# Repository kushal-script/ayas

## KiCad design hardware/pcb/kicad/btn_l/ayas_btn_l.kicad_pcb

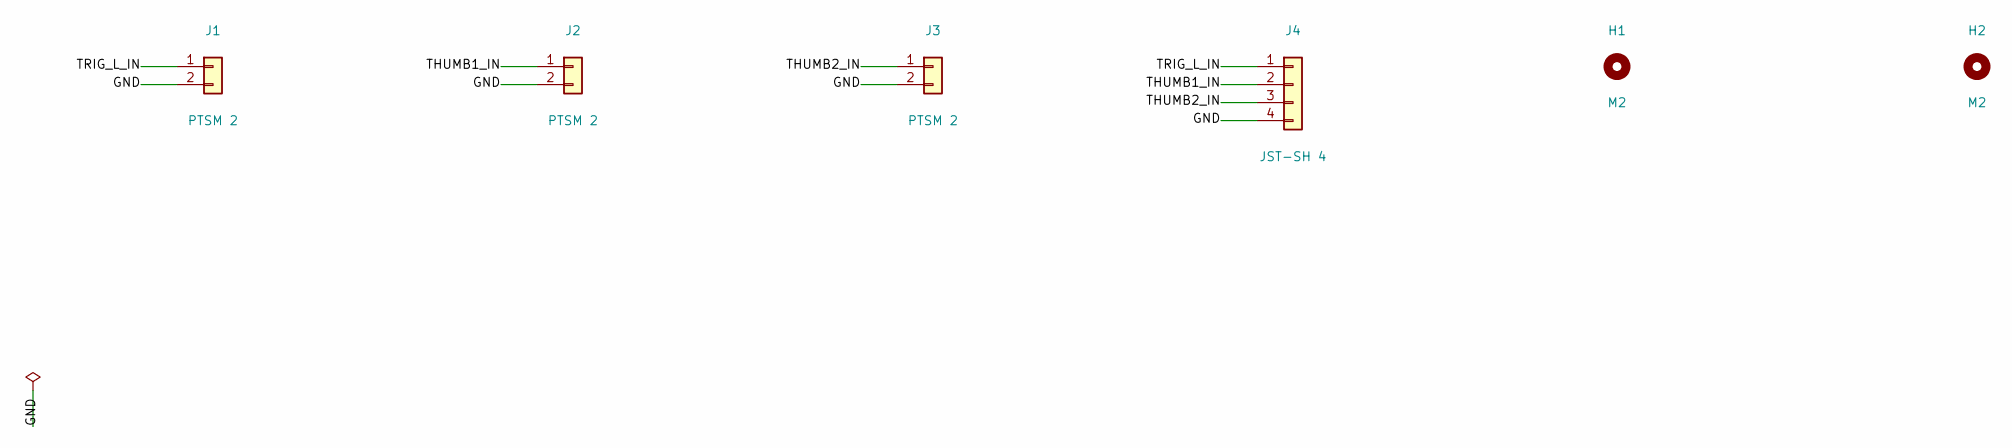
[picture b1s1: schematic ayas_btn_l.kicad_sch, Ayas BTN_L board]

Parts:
H1, H2: M2; MountingHole_2.2mm_M2
J1, J2, J3: PTSM 2; TerminalBlock_Phoenix_PTSM-0,5-2-2.5-H-THR_1x02_P2.50mm_Hor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; MPN PTSM 0,5/ 2-2,5-H THR (Phoenix Contact)
J4: JST-SH 4; JST_SH_SM04B-SRSS-TB_1x04-1MP_P1.00mm_Horizontal; MPN SM04B-SRSS-TB (JST)

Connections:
GND: J1.2, J2.2, J3.2, J4.4
THUMB1_IN: J2.1, J4.2
THUMB2_IN: J3.1, J4.3
TRIG_L_IN: J1.1, J4.1

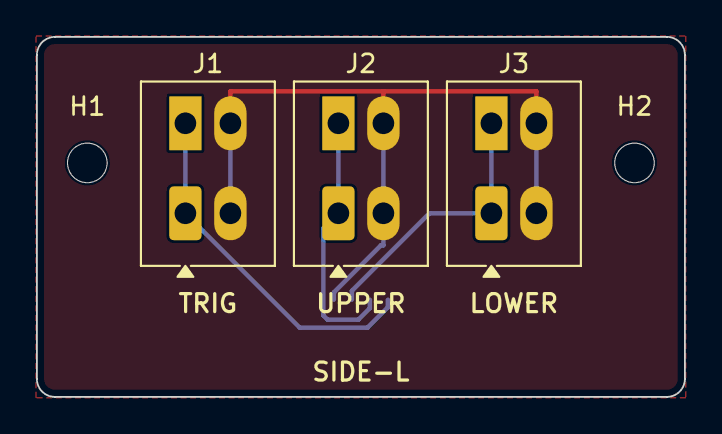
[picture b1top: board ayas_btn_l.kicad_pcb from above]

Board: 2 copper layers, 36.0 x 20.0 mm, 6 parts (1 on the bottom side), 4 nets.

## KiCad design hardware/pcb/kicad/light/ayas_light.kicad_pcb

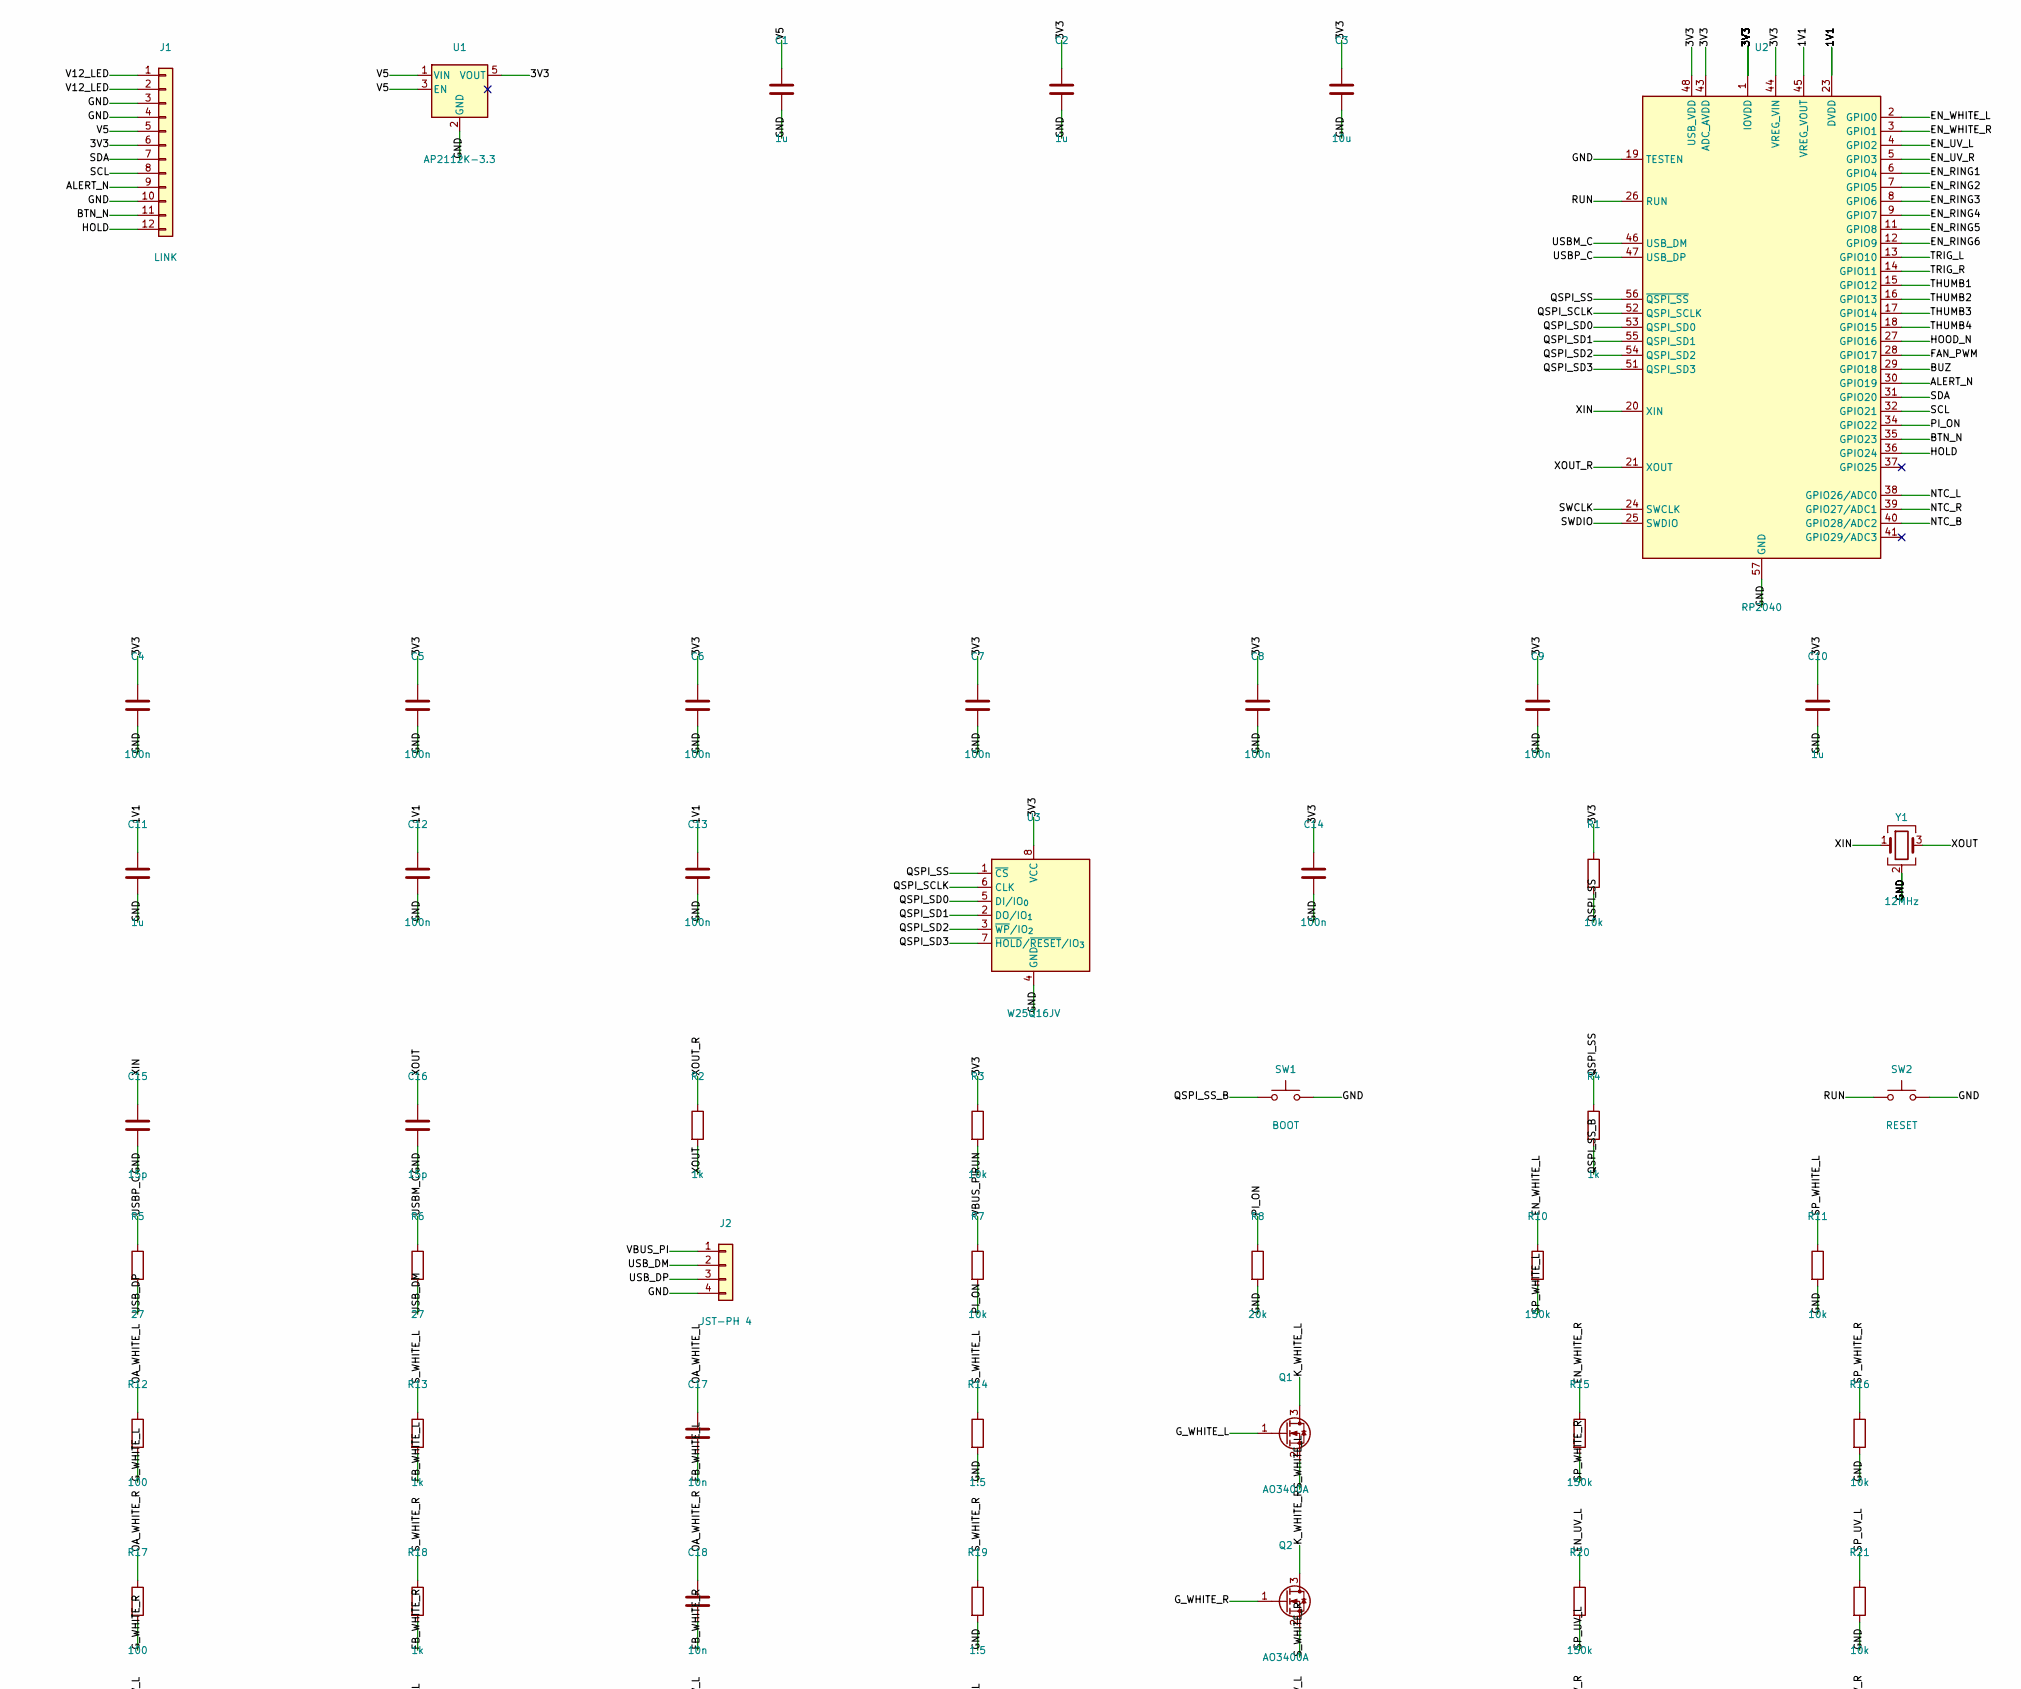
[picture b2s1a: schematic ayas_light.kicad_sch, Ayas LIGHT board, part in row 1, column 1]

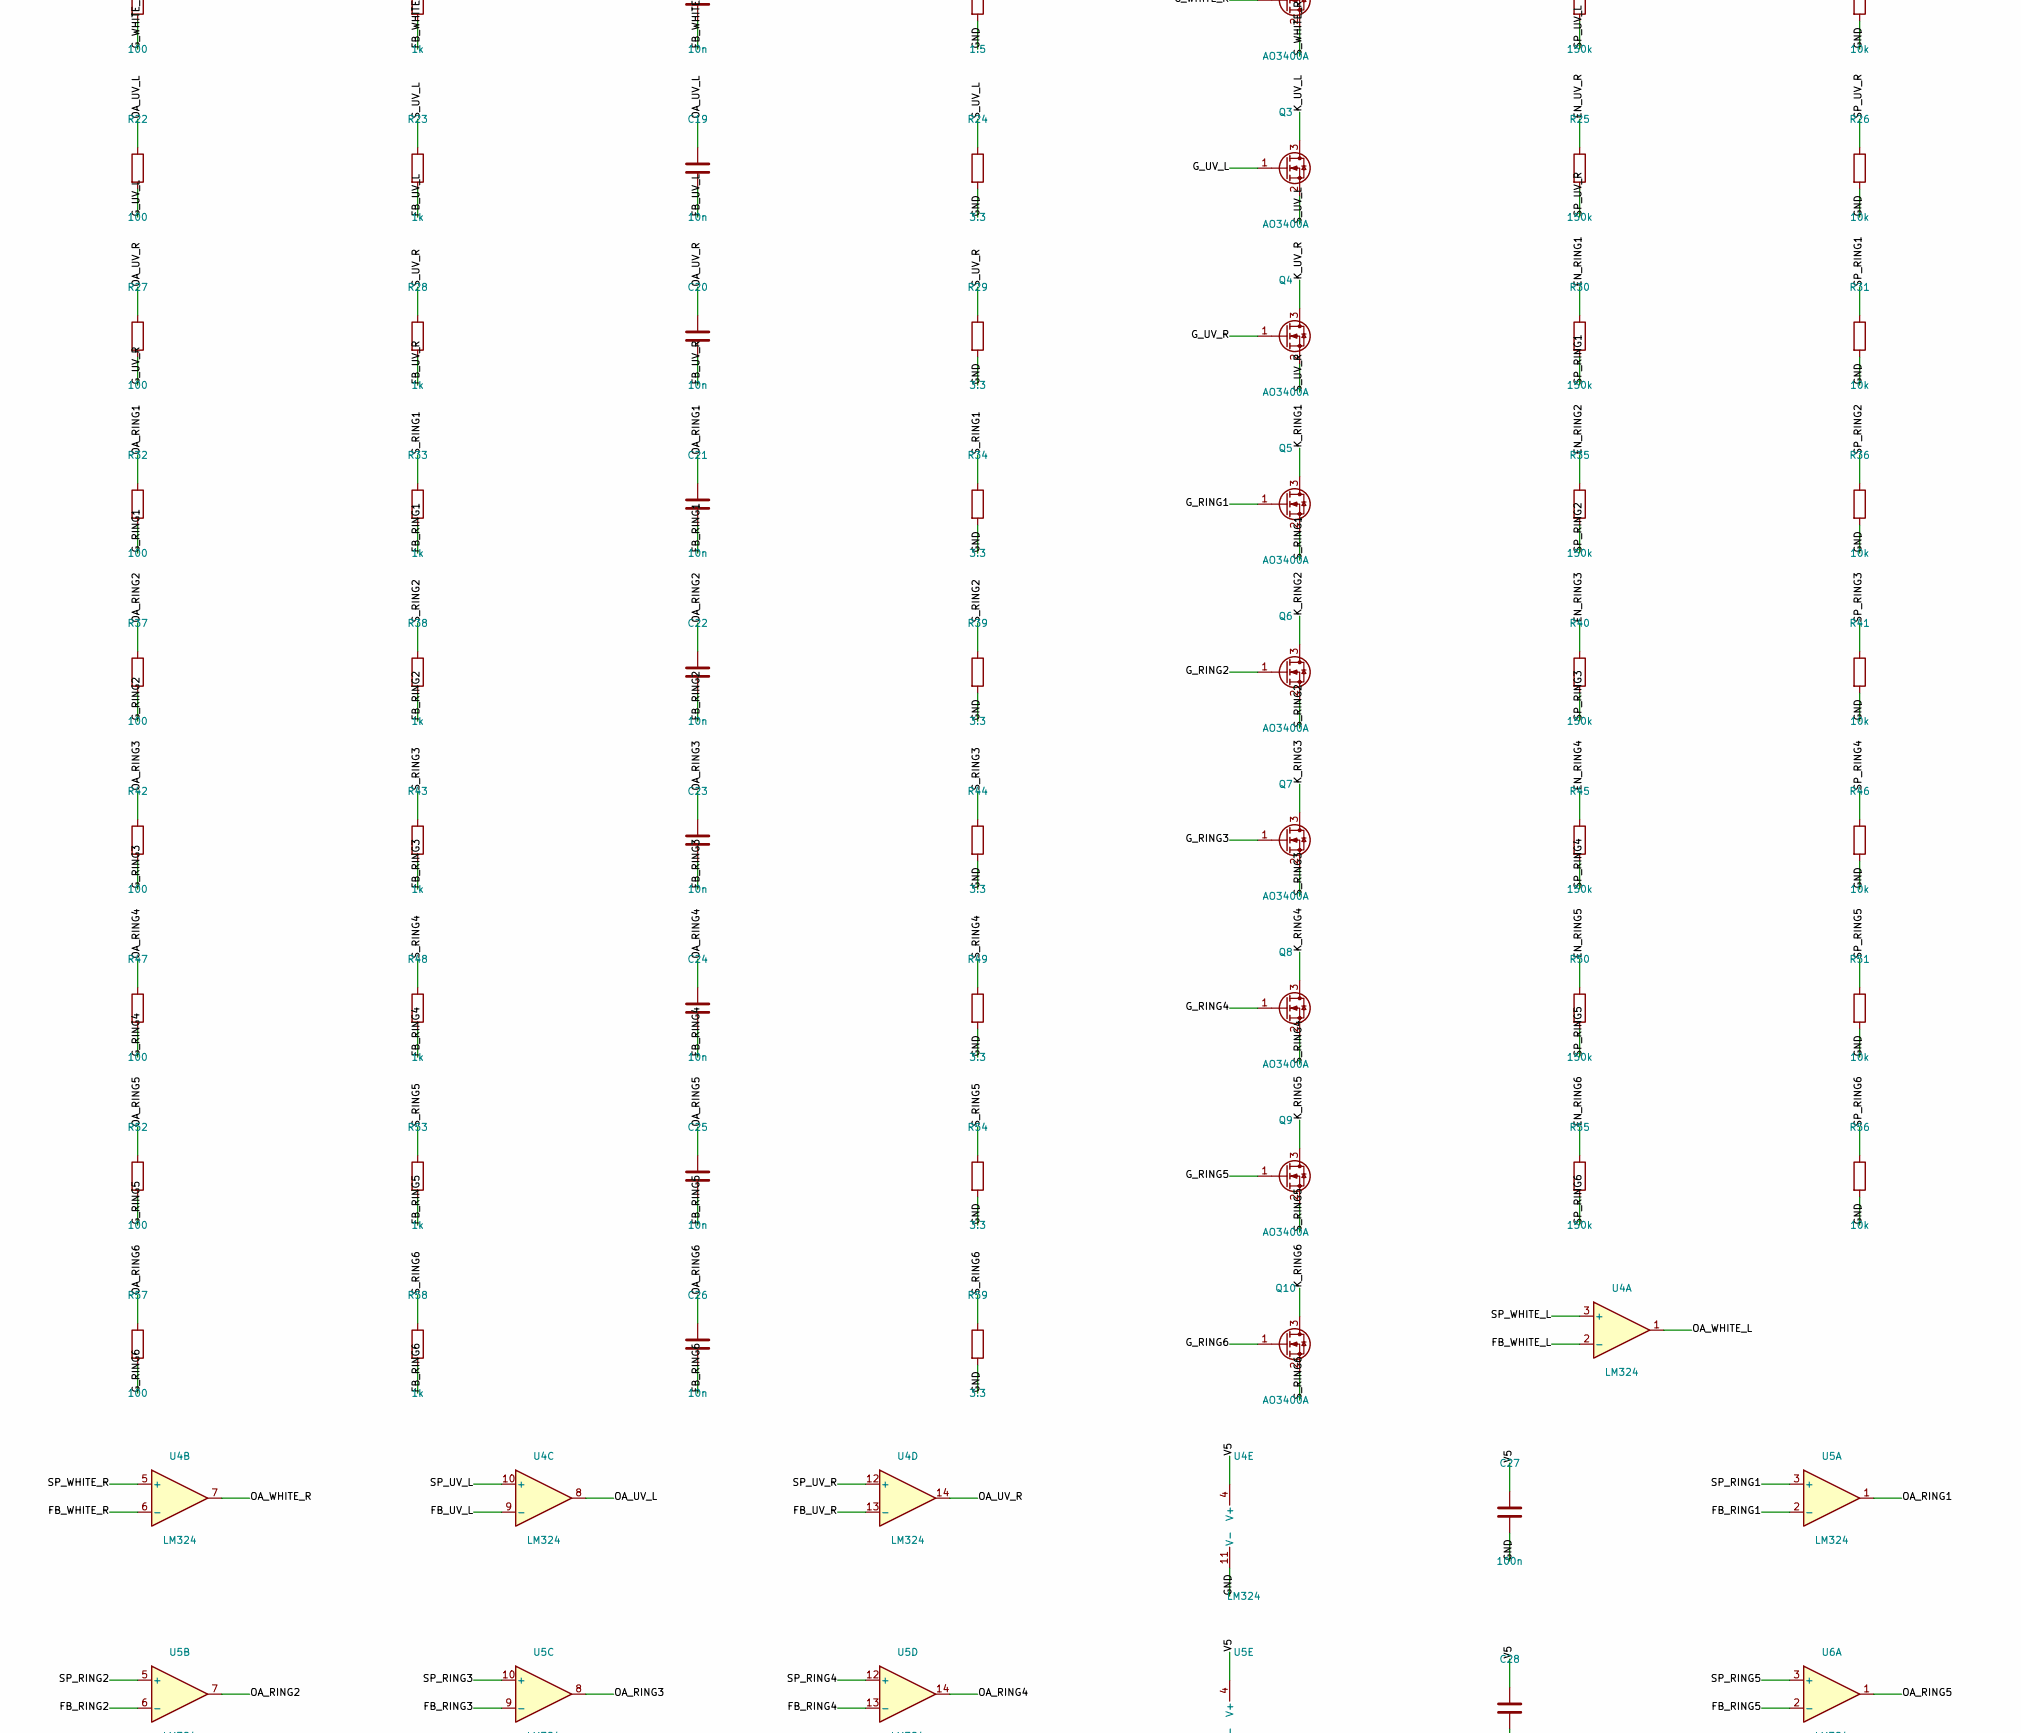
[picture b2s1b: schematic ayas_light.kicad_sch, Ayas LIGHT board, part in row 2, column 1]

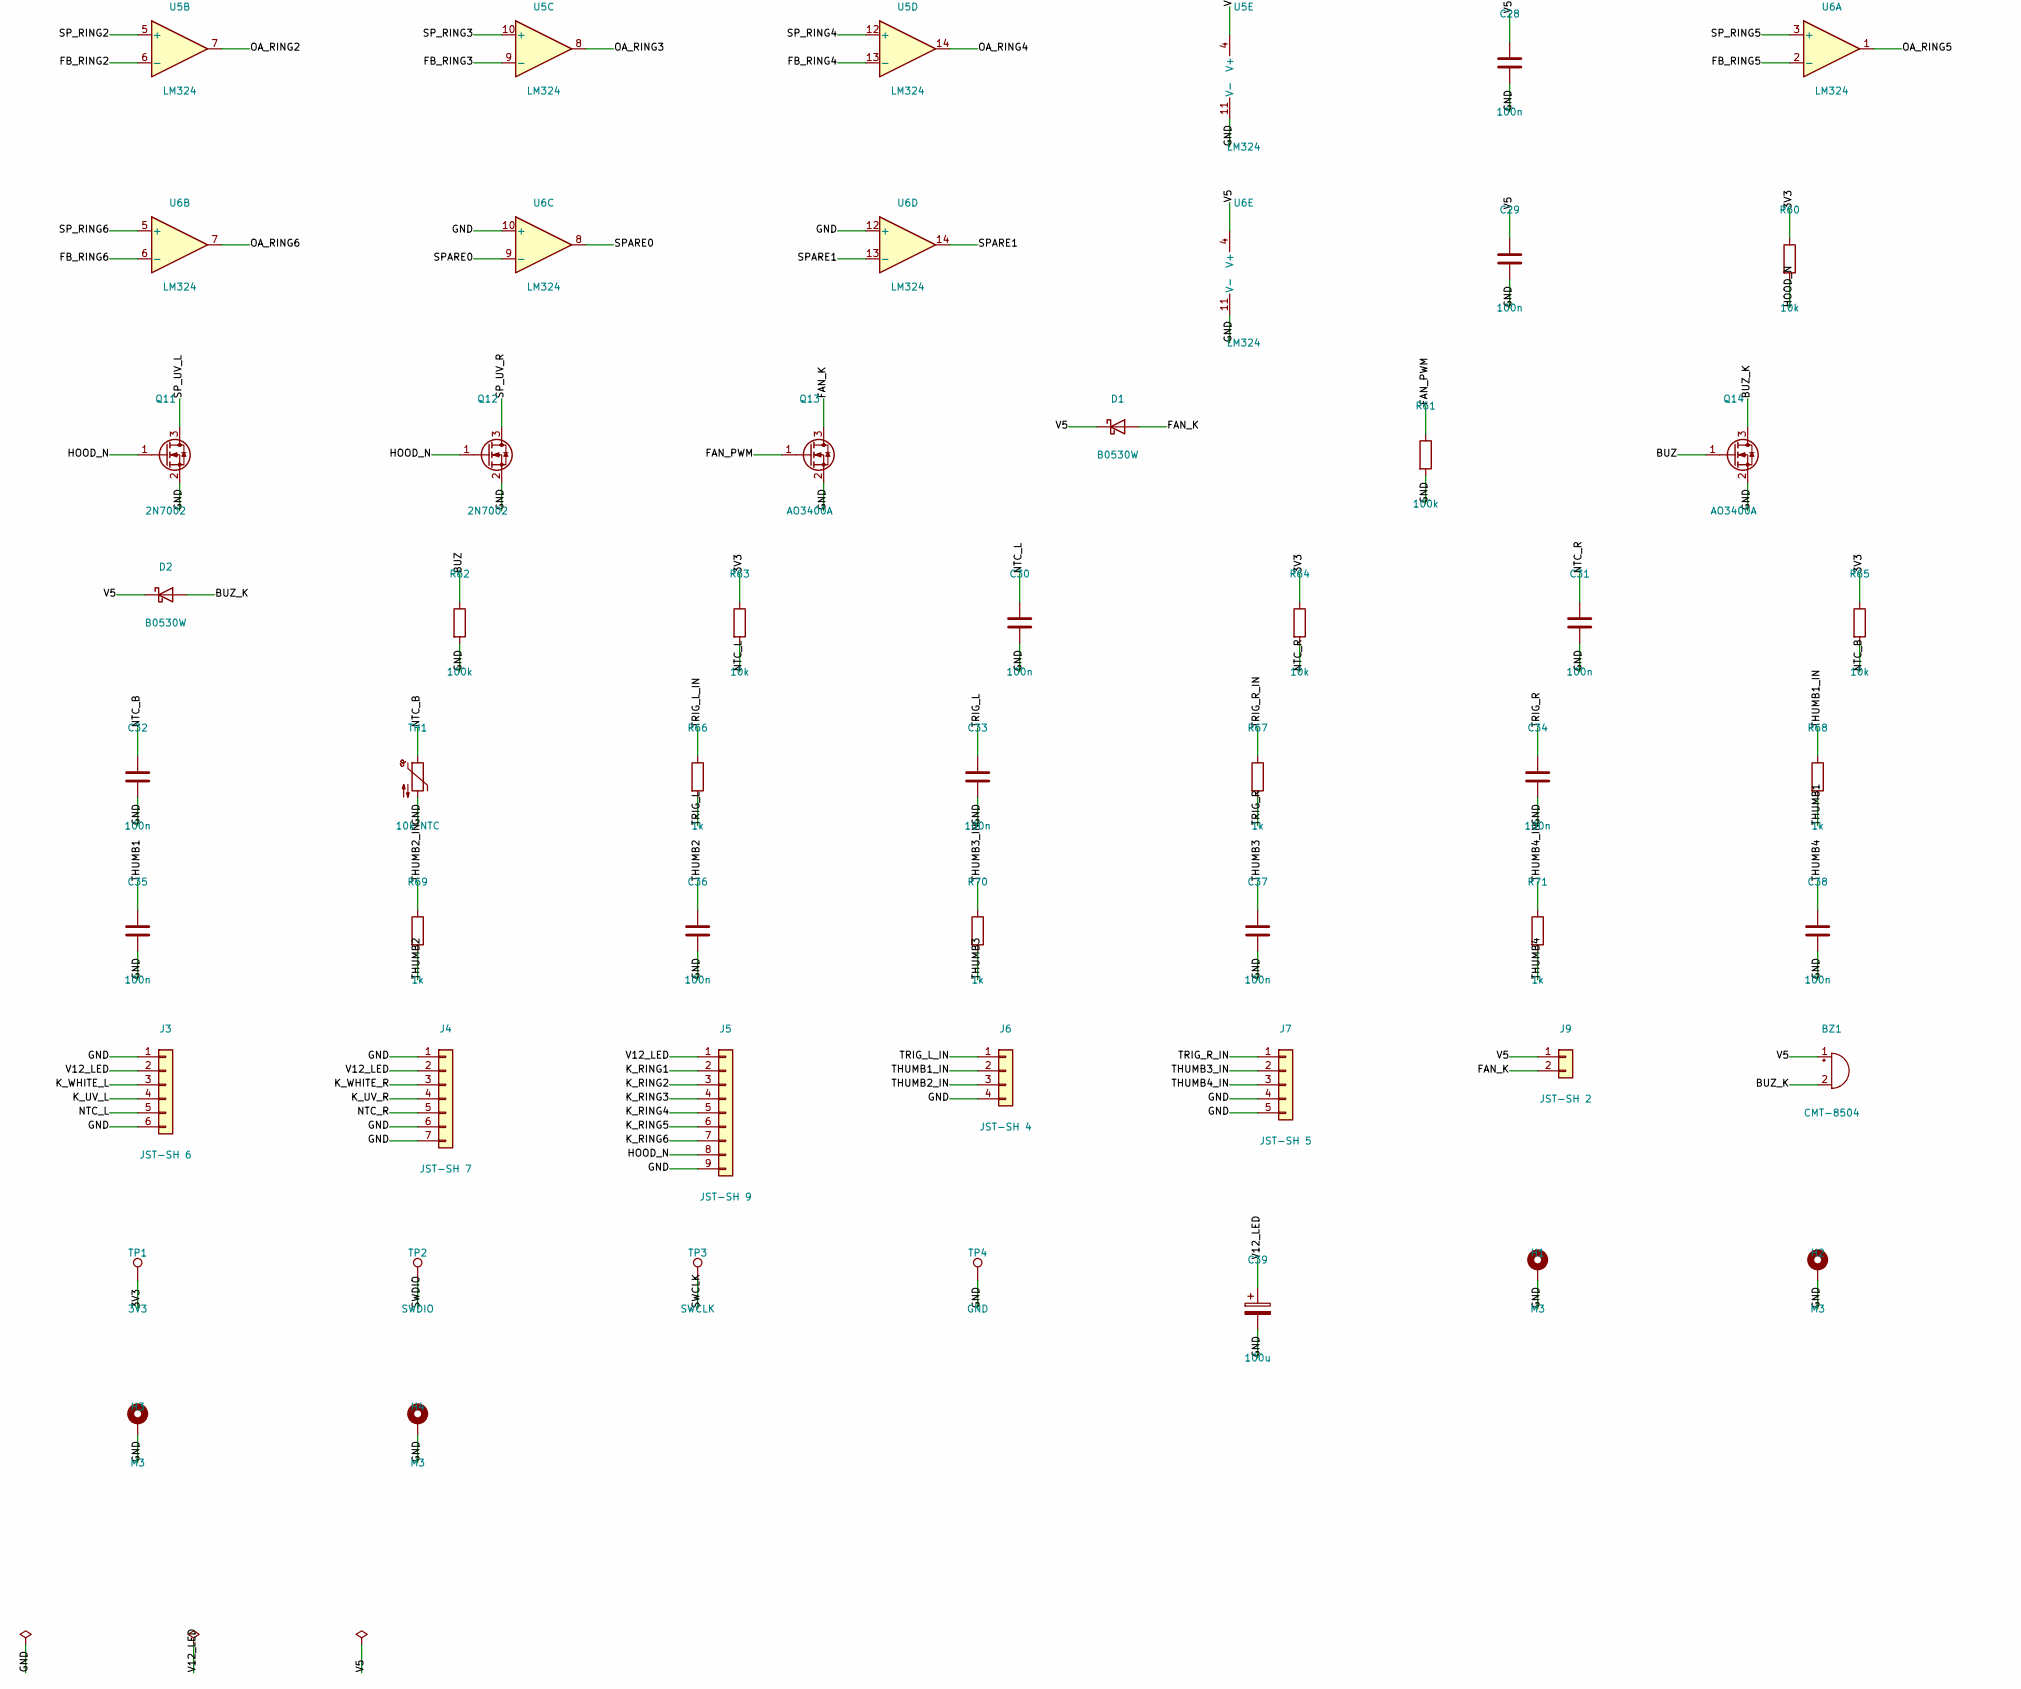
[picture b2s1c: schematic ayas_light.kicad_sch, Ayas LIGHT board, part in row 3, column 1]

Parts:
BZ1: CMT-8504; MagneticBuzzer_CUI_CMT-8504-100-SMT; MPN CMT-8504-100-SMT (CUI)
C1, C2, C10, C11: 1u; C_0603_1608Metric
C3: 10u; C_0805_2012Metric
C4, C5, C6, C7, C8, C9, C12, C13: 100n; C_0402_1005Metric
C14, C27, C28, C29, C30, C31, C32, C33, C34, C35, C36, C37, C38: 100n; C_0603_1608Metric
C15, C16: 15p; C_0603_1608Metric
C17, C18, C19, C20, C21, C22, C23, C24, C25, C26: 10n; C_0603_1608Metric
C39: 100u; CP_Elec_6.3x7.7; MPN 25 V
D1, D2: B0530W; D_SOD-123; MPN B0530W (Diodes)
H1, H2, H3, H4: M3; MountingHole_3.2mm_M3_DIN965_Pad
J1: LINK; JST_PH_B12B-PH-K_1x12_P2.00mm_Vertical; MPN B12B-PH-K-S (JST)
J2: JST-PH 4; JST_PH_B4B-PH-K_1x04_P2.00mm_Vertical; MPN B4B-PH-K-S (JST)
J3: JST-SH 6; JST_SH_SM06B-SRSS-TB_1x06-1MP_P1.00mm_Horizontal; MPN SM06B-SRSS-TB (JST)
J4: JST-SH 7; JST_SH_SM07B-SRSS-TB_1x07-1MP_P1.00mm_Horizontal; MPN SM07B-SRSS-TB (JST)
J5: JST-SH 9; JST_SH_SM09B-SRSS-TB_1x09-1MP_P1.00mm_Horizontal; MPN SM09B-SRSS-TB (JST)
J6: JST-SH 4; JST_SH_SM04B-SRSS-TB_1x04-1MP_P1.00mm_Horizontal; MPN SM04B-SRSS-TB (JST)
J7: JST-SH 5; JST_SH_SM05B-SRSS-TB_1x05-1MP_P1.00mm_Horizontal; MPN SM05B-SRSS-TB (JST)
J9: JST-SH 2; JST_SH_SM02B-SRSS-TB_1x02-1MP_P1.00mm_Horizontal; MPN SM02B-SRSS-TB (JST)
Q1, Q2, Q3, Q4, Q5, Q6, Q7, Q8, Q9, Q10, Q13, Q14: AO3400A; SOT-23; MPN AO3400A (AOS)
Q11, Q12: 2N7002; SOT-23; MPN 2N7002 (Nexperia)
R1, R3, R7, R11, R16, R21, R26, R31, R36, R41, R46, R51, R56, R60, R63, R64, R65: 10k; R_0603_1608Metric
R2, R4, R13, R18, R23, R28, R33, R38, R43, R48, R53, R58, R66, R67, R68, R69, R70, R71: 1k; R_0603_1608Metric
R5, R6: 27; R_0603_1608Metric
R8: 20k; R_0603_1608Metric
R10, R15, R20, R25, R30, R35, R40, R45, R50, R55: 150k; R_0603_1608Metric
R12, R17, R22, R27, R32, R37, R42, R47, R52, R57: 100; R_0603_1608Metric
R14, R19: 1.5; R_1206_3216Metric
R24, R29, R34, R39, R44, R49, R54, R59: 3.3; R_1206_3216Metric
R61, R62: 100k; R_0603_1608Metric
SW1: BOOT; SW_SPST_B3U-1000P; MPN B3U-1000P (Omron)
SW2: RESET; SW_SPST_B3U-1000P; MPN B3U-1000P (Omron)
TH1: 10k NTC; R_0603_1608Metric; MPN NCP18XH103F03RB (Murata)
TP1: 3V3; TestPoint_Pad_D1.5mm
TP2: SWDIO; TestPoint_Pad_D1.5mm
TP3: SWCLK; TestPoint_Pad_D1.5mm
TP4: GND; TestPoint_Pad_D1.5mm
U1: AP2112K-3.3; SOT-23-5; MPN AP2112K-3.3TRG1 (Diodes)
U2: RP2040; QFN-56-1EP_7x7mm_P0.4mm_EP3.2x3.2mm; MPN RP2040 (Raspberry Pi)
U3: W25Q16JV; SOIC-8_5.3x5.3mm_P1.27mm; MPN W25Q16JVSSIQ (Winbond)
U4, U5, U6: LM324; SOIC-14_3.9x8.7mm_P1.27mm; MPN LM324DR (TI)
Y1: 12MHz; Crystal_SMD_3225-4Pin_3.2x2.5mm; MPN ABM8-272-T3 (Abracon)

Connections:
1V1: C11.1, C12.1, C13.1, U2.23 (DVDD), U2.45 (VREG_VOUT), U2.50 (DVDD)
3V3: C2.1, C3.1, C4.1, C5.1, C6.1, C7.1, C8.1, C9.1, C10.1, C14.1, J1.6, R1.1, R3.1, R60.1, R63.1, R64.1, R65.1, TP1.1, U1.5 (VOUT), U2.1 (IOVDD), U2.10 (IOVDD), U2.22 (IOVDD), U2.33 (IOVDD), U2.42 (IOVDD), U2.43 (ADC_AVDD), U2.44 (VREG_VIN), U2.48 (USB_VDD), U2.49 (IOVDD), U3.8 (VCC)
ALERT_N: J1.9, U2.30 (GPIO19)
BTN_N: J1.11, U2.35 (GPIO23)
BUZ: Q14.1 (G), R62.1, U2.29 (GPIO18)
BUZ_K: BZ1.2 (-), D2.2 (A), Q14.3 (D)
EN_RING1: R30.1, U2.6 (GPIO4)
EN_RING2: R35.1, U2.7 (GPIO5)
EN_RING3: R40.1, U2.8 (GPIO6)
EN_RING4: R45.1, U2.9 (GPIO7)
EN_RING5: R50.1, U2.11 (GPIO8)
EN_RING6: R55.1, U2.12 (GPIO9)
EN_UV_L: R20.1, U2.4 (GPIO2)
EN_UV_R: R25.1, U2.5 (GPIO3)
EN_WHITE_L: R10.1, U2.2 (GPIO0)
EN_WHITE_R: R15.1, U2.3 (GPIO1)
FAN_K: D1.2 (A), J9.2, Q13.3 (D)
FAN_PWM: Q13.1 (G), R61.1, U2.28 (GPIO17)
FB_RING1: C21.2, R33.2, U5.2 (-)
FB_RING2: C22.2, R38.2, U5.6 (-)
FB_RING3: C23.2, R43.2, U5.9 (-)
FB_RING4: C24.2, R48.2, U5.13 (-)
FB_RING5: C25.2, R53.2, U6.2 (-)
FB_RING6: C26.2, R58.2, U6.6 (-)
FB_UV_L: C19.2, R23.2, U4.9 (-)
FB_UV_R: C20.2, R28.2, U4.13 (-)
FB_WHITE_L: C17.2, R13.2, U4.2 (-)
FB_WHITE_R: C18.2, R18.2, U4.6 (-)
GND: C1.2, C2.2, C3.2, C4.2, C5.2, C6.2, C7.2, C8.2, C9.2, C10.2, C11.2, C12.2, C13.2, C14.2, C15.2, C16.2, C27.2, C28.2, C29.2, C30.2, C31.2, C32.2, C33.2, C34.2, C35.2, C36.2, C37.2, C38.2, C39.2, H1.1, H2.1, H3.1, H4.1, J1.3, J1.4, J1.10, J2.4, J3.1, J3.6, J4.1, J4.6, J4.7, J5.9, J6.4, J7.4, J7.5, Q11.2 (S), Q12.2 (S), Q13.2 (S), Q14.2 (S), R8.2, R11.2, R14.2, R16.2, R19.2, R21.2, R24.2, R26.2, R29.2, R31.2, R34.2, R36.2, R39.2, R41.2, R44.2, R46.2, R49.2, R51.2, R54.2, R56.2, R59.2, R61.2, R62.2, SW1.2, SW2.2, TH1.2, TP4.1, U1.2 (GND), U2.19 (TESTEN), U2.57 (GND), U3.4 (GND), U4.11 (V-), U5.11 (V-), U6.10 (+), U6.11 (V-), U6.12 (+), Y1.2 (G), Y1.4 (G)
G_RING1: Q5.1 (G), R32.2
G_RING2: Q6.1 (G), R37.2
G_RING3: Q7.1 (G), R42.2
G_RING4: Q8.1 (G), R47.2
G_RING5: Q9.1 (G), R52.2
G_RING6: Q10.1 (G), R57.2
G_UV_L: Q3.1 (G), R22.2
G_UV_R: Q4.1 (G), R27.2
G_WHITE_L: Q1.1 (G), R12.2
G_WHITE_R: Q2.1 (G), R17.2
HOLD: J1.12, U2.36 (GPIO24)
HOOD_N: J5.8, Q11.1 (G), Q12.1 (G), R60.2, U2.27 (GPIO16)
K_RING1: J5.2, Q5.3 (D)
K_RING2: J5.3, Q6.3 (D)
K_RING3: J5.4, Q7.3 (D)
K_RING4: J5.5, Q8.3 (D)
K_RING5: J5.6, Q9.3 (D)
K_RING6: J5.7, Q10.3 (D)
K_UV_L: J3.4, Q3.3 (D)
K_UV_R: J4.4, Q4.3 (D)
K_WHITE_L: J3.3, Q1.3 (D)
K_WHITE_R: J4.3, Q2.3 (D)
NTC_B: C32.1, R65.2, TH1.1, U2.40 (GPIO28/ADC2)
NTC_L: C30.1, J3.5, R63.2, U2.38 (GPIO26/ADC0)
NTC_R: C31.1, J4.5, R64.2, U2.39 (GPIO27/ADC1)
OA_RING1: C21.1, R32.1, U5.1
OA_RING2: C22.1, R37.1, U5.7
OA_RING3: C23.1, R42.1, U5.8
OA_RING4: C24.1, R47.1, U5.14
OA_RING5: C25.1, R52.1, U6.1
OA_RING6: C26.1, R57.1, U6.7
OA_UV_L: C19.1, R22.1, U4.8
OA_UV_R: C20.1, R27.1, U4.14
OA_WHITE_L: C17.1, R12.1, U4.1
OA_WHITE_R: C18.1, R17.1, U4.7
PI_ON: R7.2, R8.1, U2.34 (GPIO22)
QSPI_SCLK: U2.52 (QSPI_SCLK), U3.6 (CLK)
QSPI_SD0: U2.53 (QSPI_SD0), U3.5 (DI/IO_{0})
QSPI_SD1: U2.55 (QSPI_SD1), U3.2 (DO/IO_{1})
QSPI_SD2: U2.54 (QSPI_SD2), U3.3 (~WP/IO_{2})
QSPI_SD3: U2.51 (QSPI_SD3), U3.7 (~HOLD/~RESET/IO_{3})
QSPI_SS: R1.2, R4.1, U2.56 (~QSPI_SS), U3.1 (~CS)
QSPI_SS_B: R4.2, SW1.1
RUN: R3.2, SW2.1, U2.26 (RUN)
SCL: J1.8, U2.32 (GPIO21)
SDA: J1.7, U2.31 (GPIO20)
SPARE0: U6.8, U6.9 (-)
SPARE1: U6.13 (-), U6.14
SP_RING1: R30.2, R31.1, U5.3 (+)
SP_RING2: R35.2, R36.1, U5.5 (+)
SP_RING3: R40.2, R41.1, U5.10 (+)
SP_RING4: R45.2, R46.1, U5.12 (+)
SP_RING5: R50.2, R51.1, U6.3 (+)
SP_RING6: R55.2, R56.1, U6.5 (+)
SP_UV_L: Q11.3 (D), R20.2, R21.1, U4.10 (+)
SP_UV_R: Q12.3 (D), R25.2, R26.1, U4.12 (+)
SP_WHITE_L: R10.2, R11.1, U4.3 (+)
SP_WHITE_R: R15.2, R16.1, U4.5 (+)
SWCLK: TP3.1, U2.24 (SWCLK)
SWDIO: TP2.1, U2.25 (SWDIO)
S_RING1: Q5.2 (S), R33.1, R34.1
S_RING2: Q6.2 (S), R38.1, R39.1
S_RING3: Q7.2 (S), R43.1, R44.1
S_RING4: Q8.2 (S), R48.1, R49.1
S_RING5: Q9.2 (S), R53.1, R54.1
S_RING6: Q10.2 (S), R58.1, R59.1
S_UV_L: Q3.2 (S), R23.1, R24.1
S_UV_R: Q4.2 (S), R28.1, R29.1
S_WHITE_L: Q1.2 (S), R13.1, R14.1
S_WHITE_R: Q2.2 (S), R18.1, R19.1
THUMB1: C35.1, R68.2, U2.15 (GPIO12)
THUMB1_IN: J6.2, R68.1
THUMB2: C36.1, R69.2, U2.16 (GPIO13)
THUMB2_IN: J6.3, R69.1
THUMB3: C37.1, R70.2, U2.17 (GPIO14)
THUMB3_IN: J7.2, R70.1
THUMB4: C38.1, R71.2, U2.18 (GPIO15)
THUMB4_IN: J7.3, R71.1
TRIG_L: C33.1, R66.2, U2.13 (GPIO10)
TRIG_L_IN: J6.1, R66.1
TRIG_R: C34.1, R67.2, U2.14 (GPIO11)
TRIG_R_IN: J7.1, R67.1
USBM_C: R6.1, U2.46 (USB_DM)
USBP_C: R5.1, U2.47 (USB_DP)
USB_DM: J2.2, R6.2
USB_DP: J2.3, R5.2
V5: BZ1.1 (+), C1.1, C27.1, C28.1, C29.1, D1.1 (K), D2.1 (K), J1.5, J9.1, U1.1 (VIN), U1.3 (EN), U4.4 (V+), U5.4 (V+), U6.4 (V+)
V12_LED: C39.1, J1.1, J1.2, J3.2, J4.2, J5.1
VBUS_PI: J2.1, R7.1
XIN: C15.1, U2.20 (XIN), Y1.1
XOUT: C16.1, R2.2, Y1.3
XOUT_R: R2.1, U2.21 (XOUT)

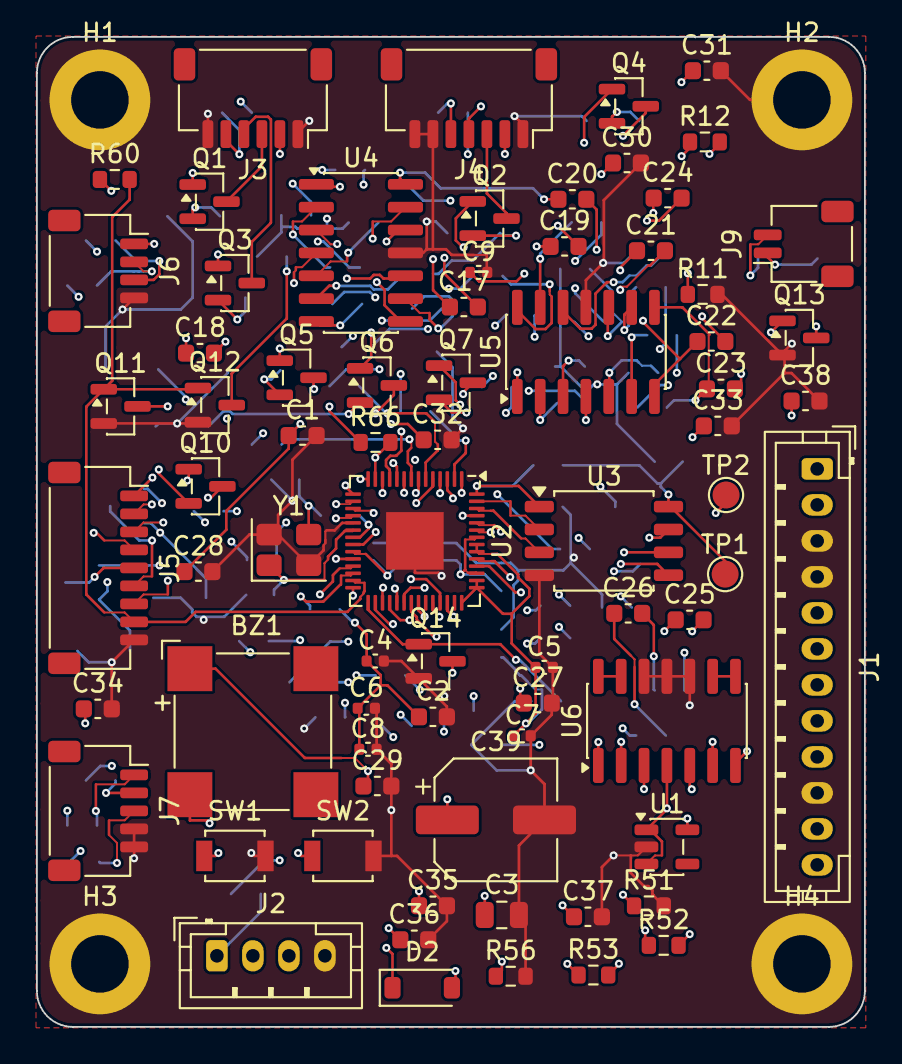
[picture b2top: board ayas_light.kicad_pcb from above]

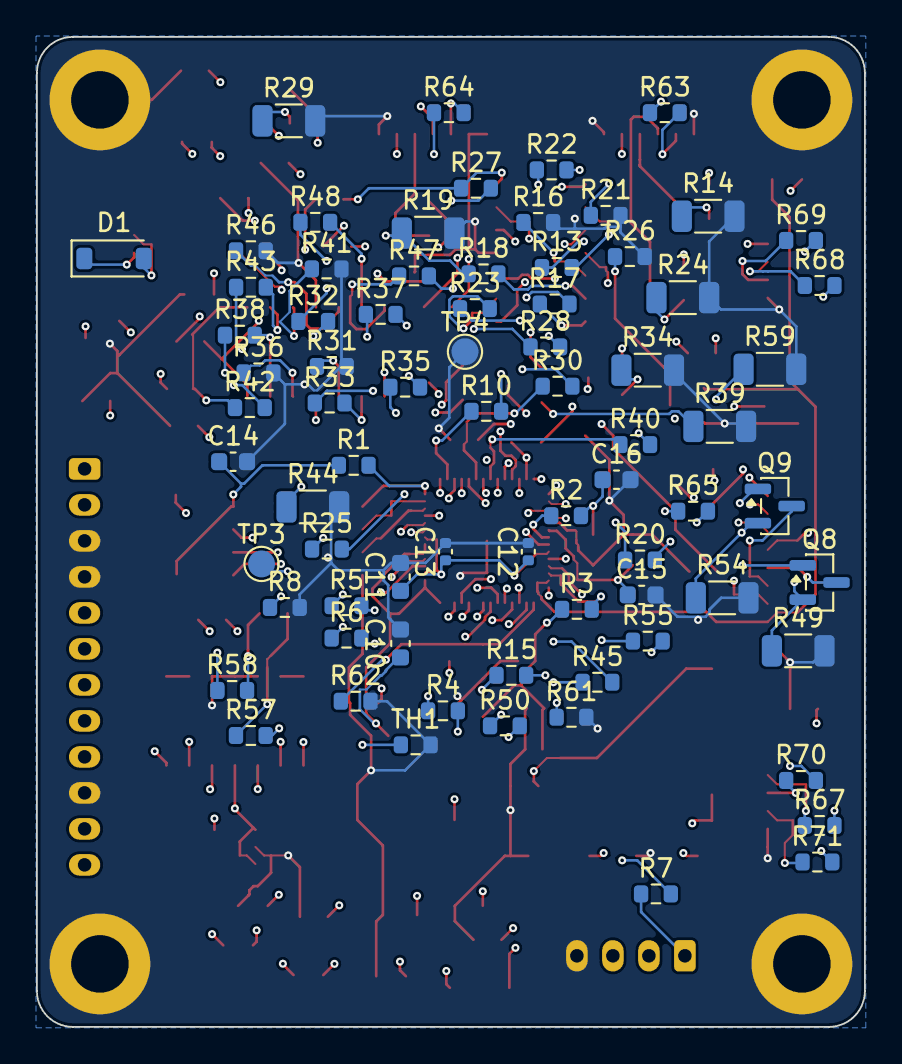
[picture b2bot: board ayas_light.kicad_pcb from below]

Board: 6 copper layers, 46.0 x 55.0 mm, 152 parts (75 on the bottom side), 121 nets.
